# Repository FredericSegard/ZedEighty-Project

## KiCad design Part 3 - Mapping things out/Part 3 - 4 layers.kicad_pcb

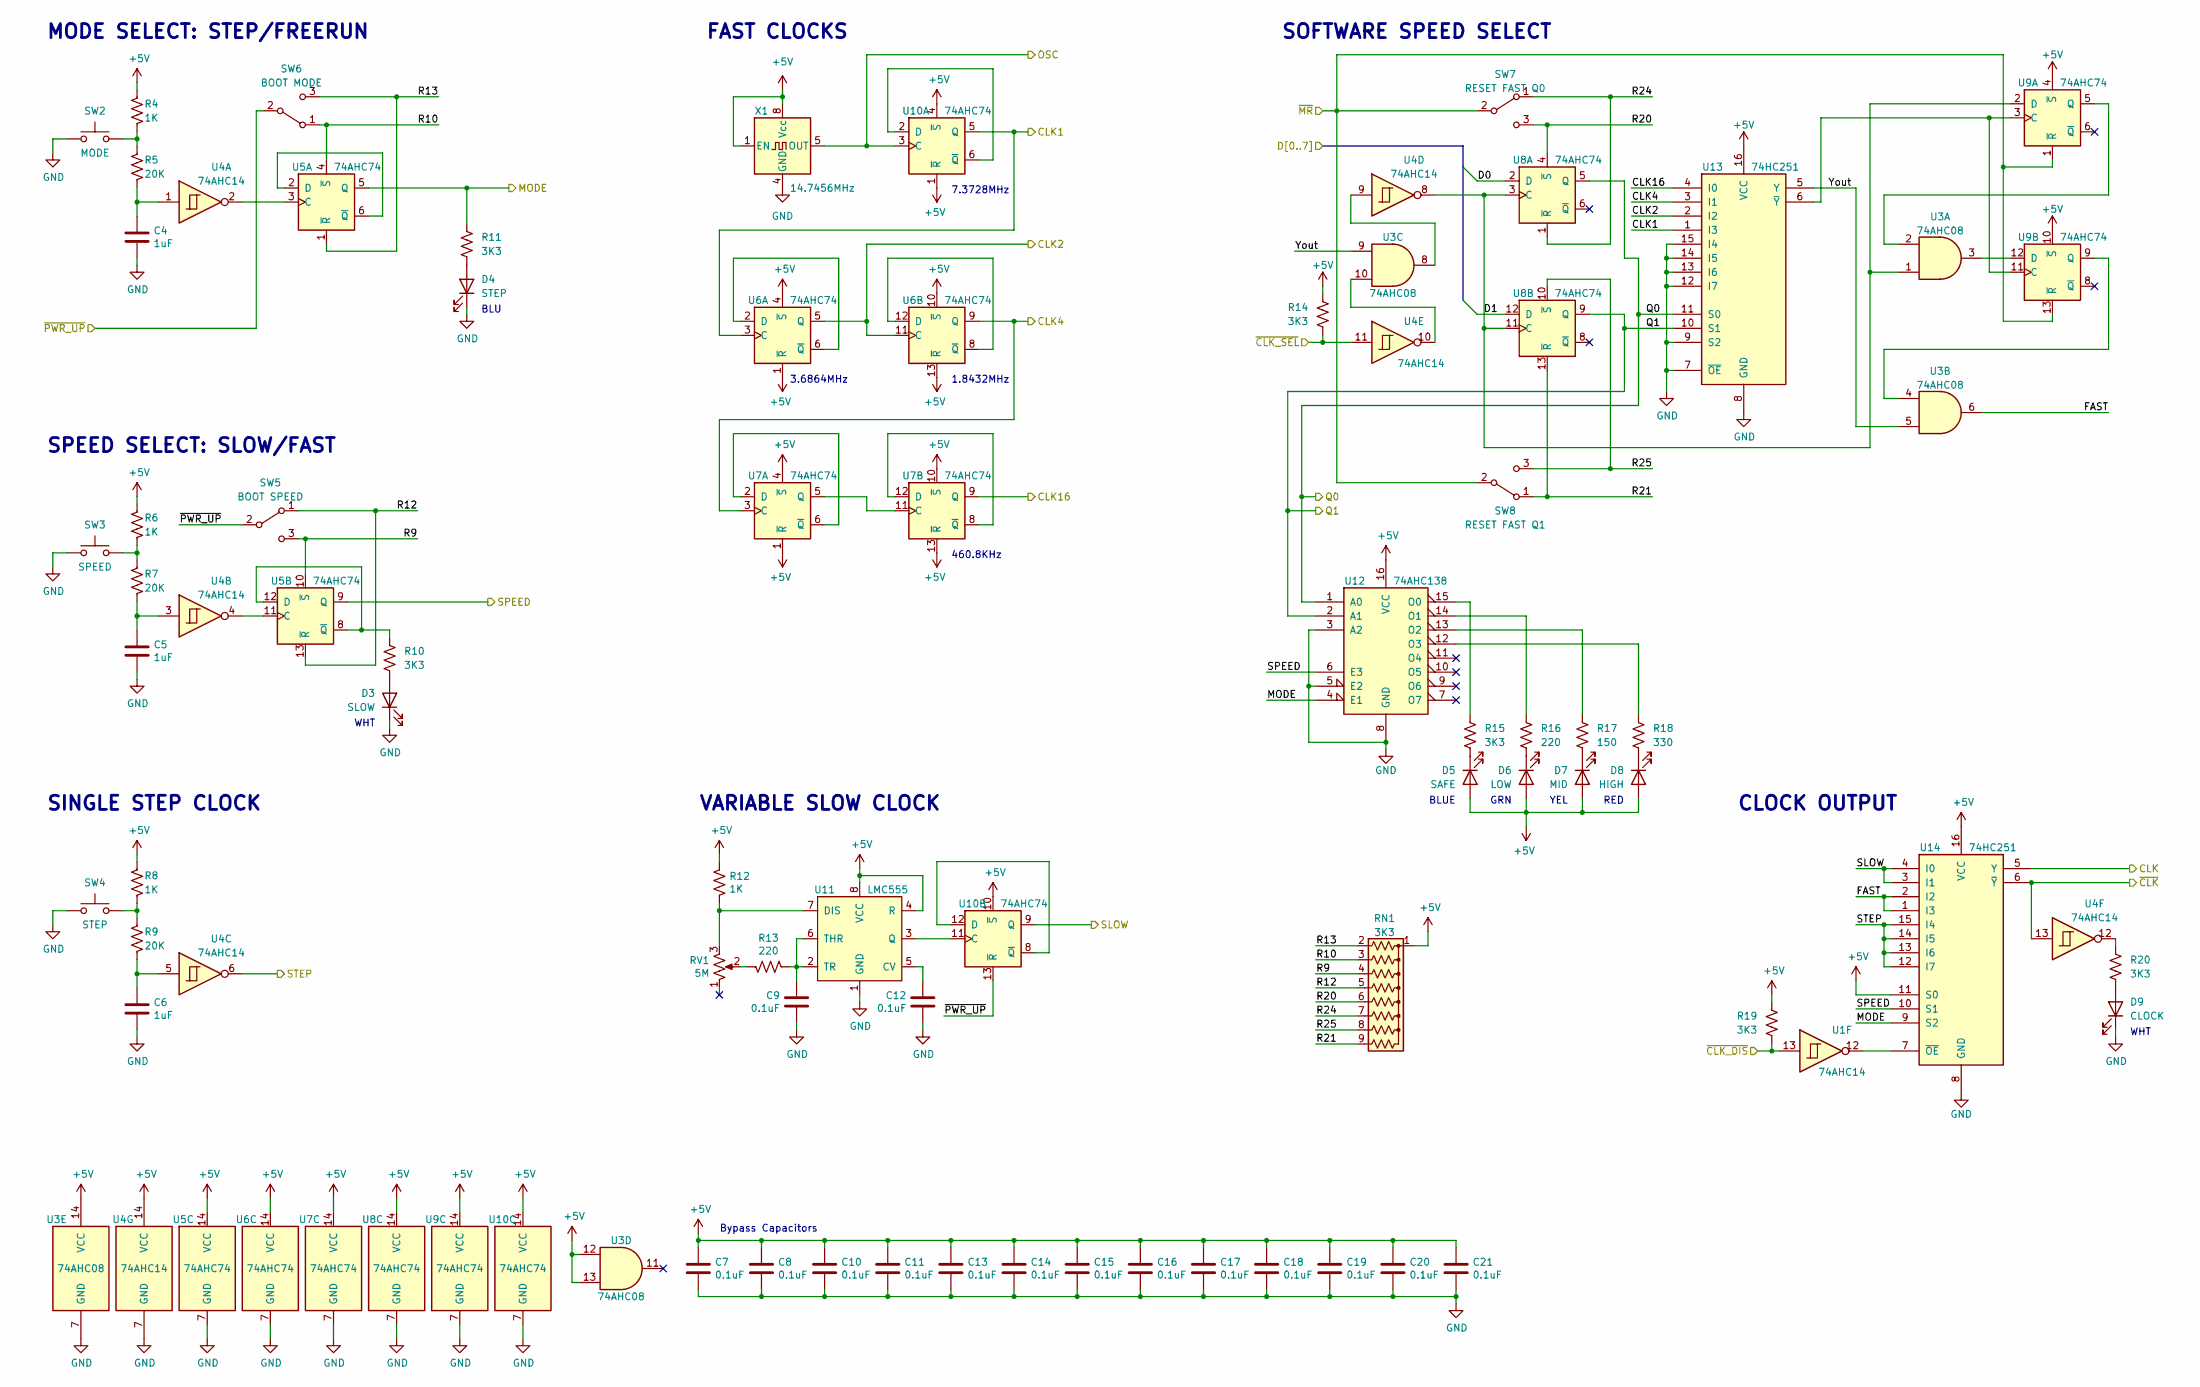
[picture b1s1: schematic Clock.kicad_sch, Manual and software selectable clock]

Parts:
C4, C5, C6: 1uF; C_Disc_D3.0mm_W1.6mm_P2.50mm
C7, C8, C9, C10, C11, C12, C13, C14, C15, C16, C17, C18, C19, C20, C21: 0.1uF; C_Disc_D3.0mm_W1.6mm_P2.50mm
D3: SLOW; LED_D3.0mm_Horizontal_O1.27mm_Z2.0mm_Clear
D4: STEP; LED_D3.0mm_Horizontal_O1.27mm_Z2.0mm_Clear
D5: SAFE; LED_D3.0mm_Horizontal_O1.27mm_Z2.0mm_Clear
D6: LOW; LED_D3.0mm_Horizontal_O1.27mm_Z2.0mm_Clear
D7: MID; LED_D3.0mm_Horizontal_O1.27mm_Z2.0mm_Clear
D8: HIGH; LED_D3.0mm_Horizontal_O1.27mm_Z2.0mm_Clear
D9: CLOCK; LED_D3.0mm_Horizontal_O1.27mm_Z2.0mm_Clear
R4, R6, R8, R12: 1K; R_Axial_DIN0207_L6.3mm_D2.5mm_P10.16mm_Horizontal
R5, R7, R9: 20K; R_Axial_DIN0207_L6.3mm_D2.5mm_P10.16mm_Horizontal
R10, R11, R14, R15, R19, R20: 3K3; R_Axial_DIN0207_L6.3mm_D2.5mm_P10.16mm_Horizontal
R13, R16: 220; R_Axial_DIN0207_L6.3mm_D2.5mm_P10.16mm_Horizontal
R17: 150; R_Axial_DIN0207_L6.3mm_D2.5mm_P10.16mm_Horizontal
R18: 330; R_Axial_DIN0207_L6.3mm_D2.5mm_P10.16mm_Horizontal
RN1: 3K3; R_Array_SIP9
RV1: 5M; Potentiometer_Bourns_3006P_Horizontal
SW2: MODE; SW_Tactile_SPST_Angled_PTS645Vx58-2LFS
SW3: SPEED; SW_Tactile_SPST_Angled_PTS645Vx58-2LFS
SW4: STEP; SW_Tactile_SPST_Angled_PTS645Vx58-2LFS
SW5: BOOT SPEED; Microswitch_4.7mm_spacing
SW6: BOOT MODE; Microswitch_4.7mm_spacing
SW7: RESET FAST Q0; Microswitch_4.7mm_spacing
SW8: RESET FAST Q1; Microswitch_4.7mm_spacing
U1, U4: 74AHC14; DIP-14_W7.62mm_Socket
U3: 74AHC08; DIP-14_W7.62mm_Socket
U5, U6, U7, U8, U9, U10: 74AHC74; DIP-14_W7.62mm_Socket
U11: LMC555; DIP-8_W7.62mm_Socket
U12: 74AHC138; DIP-16_W7.62mm_Socket
U13, U14: 74HC251; DIP-16_W7.62mm_Socket
X1: 14.7456MHz; DIP-8-4_W7.62mm_Oscillator_Socket

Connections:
/CLK: U14.5 (Y); also elsewhere on the board
/CLK1: U6.3 (C), U10.5 (Q), U13.1 (I3); also elsewhere on the board
/CLK2: U6.5 (Q), U6.11 (C), U13.2 (I2); also elsewhere on the board
/CLK4: U6.9 (Q), U7.3 (C), U13.3 (I1); also elsewhere on the board
/CLK16: U7.9 (Q), U13.4 (I0); also elsewhere on the board
/Clock/FAST: U3.6, U14.1 (I3), U14.2 (I2)
/Clock/R9: RN1.4 (R3), SW5.3 (C), U5.10 (~S)
/Clock/R10: RN1.3 (R2), SW6.1 (A), U5.4 (~S)
/Clock/R12: RN1.5 (R4), SW5.1 (A), U5.13 (~R)
/Clock/R13: RN1.2 (R1), SW6.3 (C), U5.1 (~R)
/Clock/R20: RN1.6 (R5), SW7.3 (C), U8.4 (~S)
/Clock/R21: RN1.9 (R8), SW8.1 (A), U8.13 (~R)
/Clock/R24: RN1.7 (R6), SW7.1 (A), U8.1 (~R)
/Clock/R25: RN1.8 (R7), SW8.3 (C), U8.10 (~S)
/Clock/Yout: U3.5, U3.9, U13.5 (Y)
/D0: U8.2 (D); also elsewhere on the board
/D1: U8.12 (D); also elsewhere on the board
/MODE: R11.1, U5.5 (Q), U12.4 (E1), U14.9 (S2); also elsewhere on the board
/OSC: U10.3 (C), X1.5 (OUT); also elsewhere on the board
/Q0: U8.5 (Q), U12.1 (A0), U13.11 (S0); also elsewhere on the board
/Q1: U8.9 (Q), U12.2 (A1), U13.10 (S1); also elsewhere on the board
/SLOW: U10.9 (Q), U14.3 (I1), U14.4 (I0); also elsewhere on the board
/SPEED: U5.9 (Q), U12.6 (E3), U14.10 (S1); also elsewhere on the board
/STEP: U4.6, U14.12 (I7), U14.13 (I6), U14.14 (I5), U14.15 (I4); also elsewhere on the board
/~CLK_SEL: R14.1, U4.11; also elsewhere on the board
/~CLK: U4.13, U14.6 (~Y); also elsewhere on the board
/~PWR_UP: SW5.2 (B), SW6.2 (B), U10.13 (~R); also elsewhere on the board
unnamed: C5.1, R7.1, U4.3
unnamed: C9.1, R13.2, U11.2 (TR), U11.6 (THR)
unnamed: C12.1, U11.5 (CV)
unnamed: D3.2 (A), R10.2
unnamed: D4.2 (A), R11.2
unnamed: D5.1 (K), R15.2
unnamed: D6.1 (K), R16.2
unnamed: D7.1 (K), R17.2
unnamed: D8.1 (K), R18.2
unnamed: D9.2 (A), R20.2
unnamed: R8.2, R9.2, SW4.1
unnamed: R10.1, U5.8 (~Q), U5.12 (D)
unnamed: R12.2, RV1.3, U11.7 (DIS)
unnamed: R13.1, RV1.2
unnamed: R15.1, U12.15 (O0)
unnamed: R16.1, U12.14 (O1)
unnamed: R17.1, U12.13 (O2)
unnamed: R18.1, U12.12 (O3)
unnamed: R20.1, U4.12
unnamed: U1.12, U14.7 (~OE)
unnamed: U3.1, U4.8, U8.3 (C), U8.11 (C), U9.2 (D)
unnamed: U3.2, U9.5 (Q)
unnamed: U3.3, U9.12 (D)
unnamed: U3.4, U9.9 (Q)
unnamed: U3.8, U4.9
unnamed: U3.10, U4.10
unnamed: U4.2, U5.3 (C)
unnamed: U4.4, U5.11 (C)
unnamed: U5.2 (D), U5.6 (~Q)
unnamed: U6.2 (D), U6.6 (~Q)
unnamed: U6.8 (~Q), U6.12 (D)
unnamed: U7.2 (D), U7.6 (~Q)
unnamed: U7.5 (Q), U7.11 (C)
unnamed: U7.8 (~Q), U7.12 (D)
unnamed: U10.2 (D), U10.6 (~Q)
unnamed: U10.11 (C), U11.3 (Q)
unnamed: U10.8 (~Q), U10.12 (D)
unnamed: U9.3 (C), U9.11 (C), U13.6 (~Y)

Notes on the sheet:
3.6864MHz
VARIABLE SLOW CLOCK
SPEED SELECT: SLOW/FAST
Bypass Capacitors
MODE SELECT: STEP/FREERUN
RED
FAST CLOCKS
SOFTWARE SPEED SELECT
CLOCK OUTPUT
GRN
WHT
1.8432MHz
BLU
7.3728MHz
YEL
BLUE
460.8KHz
SINGLE STEP CLOCK

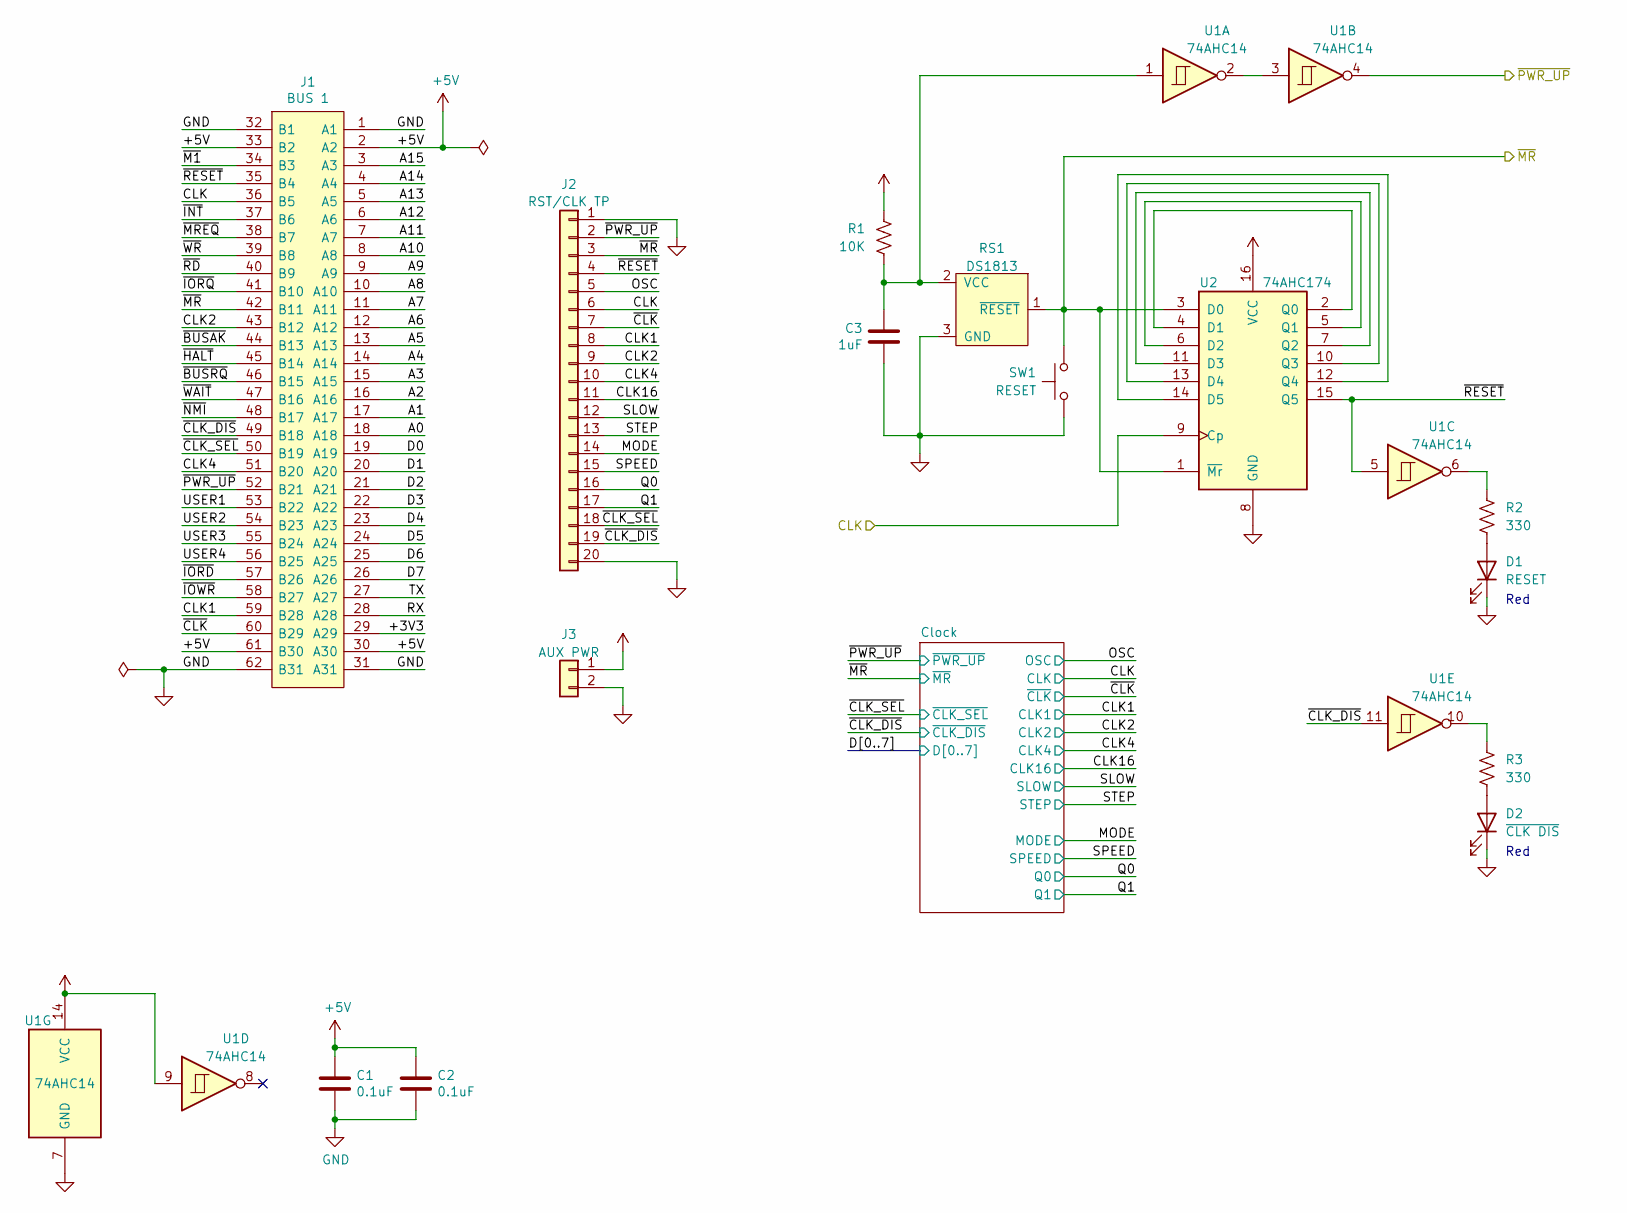
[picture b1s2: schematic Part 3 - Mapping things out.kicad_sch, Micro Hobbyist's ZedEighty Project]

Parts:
C1, C2: 0.1uF; C_Disc_D3.0mm_W2.0mm_P2.50mm
C3: 1uF; C_Disc_D3.0mm_W2.0mm_P2.50mm
D1: RESET; LED_D3.0mm_Horizontal_O1.27mm_Z2.0mm_Clear
D2: ~{CLK DIS}; LED_D3.0mm_Horizontal_O1.27mm_Z2.0mm_Clear
J1: BUS 1; BUS_XT; Mouser Part Number 571-6-5530843-5
J2: RST/CLK TP; PinSocket_1x20_P2.54mm_Horizontal
J3: AUX PWR; PinSocket_1x02_P2.54mm_Horizontal
R1: 10K; R_Axial_DIN0207_L6.3mm_D2.5mm_P10.16mm_Horizontal
R2, R3: 330; R_Axial_DIN0207_L6.3mm_D2.5mm_P10.16mm_Horizontal
RS1: DS1813; TO-92L_Inline_Wide
SW1: RESET; SW_Tactile_SPST_Angled_PTS645Vx58-2LFS
U1: 74AHC14; DIP-14_W7.62mm_Socket
U2: 74AHC174; DIP-16_W7.62mm_Socket

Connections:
/+3V3: J1.29 (A29)
/A0: J1.18 (A18)
/A1: J1.17 (A17)
/A2: J1.16 (A16)
/A3: J1.15 (A15)
/A4: J1.14 (A14)
/A5: J1.13 (A13)
/A6: J1.12 (A12)
/A7: J1.11 (A11)
/A8: J1.10 (A10)
/A9: J1.9 (A9)
/A10: J1.8 (A8)
/A11: J1.7 (A7)
/A12: J1.6 (A6)
/A13: J1.5 (A5)
/A14: J1.4 (A4)
/A15: J1.3 (A3)
/CLK: J1.36 (B5), J2.6, U2.9 (Cp); also elsewhere on the board
/CLK1: J1.59 (B28), J2.8; also elsewhere on the board
/CLK2: J1.43 (B12), J2.9; also elsewhere on the board
/CLK4: J1.51 (B20), J2.10; also elsewhere on the board
/CLK16: J2.11; also elsewhere on the board
/D0: J1.19 (A19); also elsewhere on the board
/D1: J1.20 (A20); also elsewhere on the board
/D2: J1.21 (A21)
/D3: J1.22 (A22)
/D4: J1.23 (A23)
/D5: J1.24 (A24)
/D6: J1.25 (A25)
/D7: J1.26 (A26)
/MODE: J2.14; also elsewhere on the board
/OSC: J2.5; also elsewhere on the board
/Q0: J2.16; also elsewhere on the board
/Q1: J2.17; also elsewhere on the board
/RX: J1.28 (A28)
/SLOW: J2.12; also elsewhere on the board
/SPEED: J2.15; also elsewhere on the board
/STEP: J2.13; also elsewhere on the board
/TX: J1.27 (A27)
/USER1: J1.53 (B22)
/USER2: J1.54 (B23)
/USER3: J1.55 (B24)
/USER4: J1.56 (B25)
/USER5: J1.57 (B26)
/USER6: J1.58 (B27)
/~BUSAK: J1.44 (B13)
/~BUSRQ: J1.46 (B15)
/~CLK_SEL: J1.50 (B19), J2.18; also elsewhere on the board
/~CLK: J1.60 (B29), J2.7; also elsewhere on the board
/~HALT: J1.45 (B14)
/~INT: J1.37 (B6)
/~IORQ: J1.41 (B10)
/~M1: J1.34 (B3)
/~MREQ: J1.38 (B7)
/~NMI: J1.48 (B17)
/~PWR_UP: J1.52 (B21), J2.2, U1.4; also elsewhere on the board
/~RD: J1.40 (B9)
/~RESET: J1.35 (B4), J2.4, U1.5, U2.15 (Q5)
/~WAIT: J1.47 (B16)
/~WR: J1.39 (B8)
unnamed: D1.2 (A), R2.2
unnamed: R3.1, U1.10
unnamed: U1.2, U1.3
unnamed: U2.2 (Q0), U2.4 (D1)
unnamed: U2.5 (Q1), U2.6 (D2)
unnamed: U2.10 (Q3), U2.13 (D4)
unnamed: U2.7 (Q2), U2.11 (D3)
unnamed: U2.12 (Q4), U2.14 (D5)

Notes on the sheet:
Red

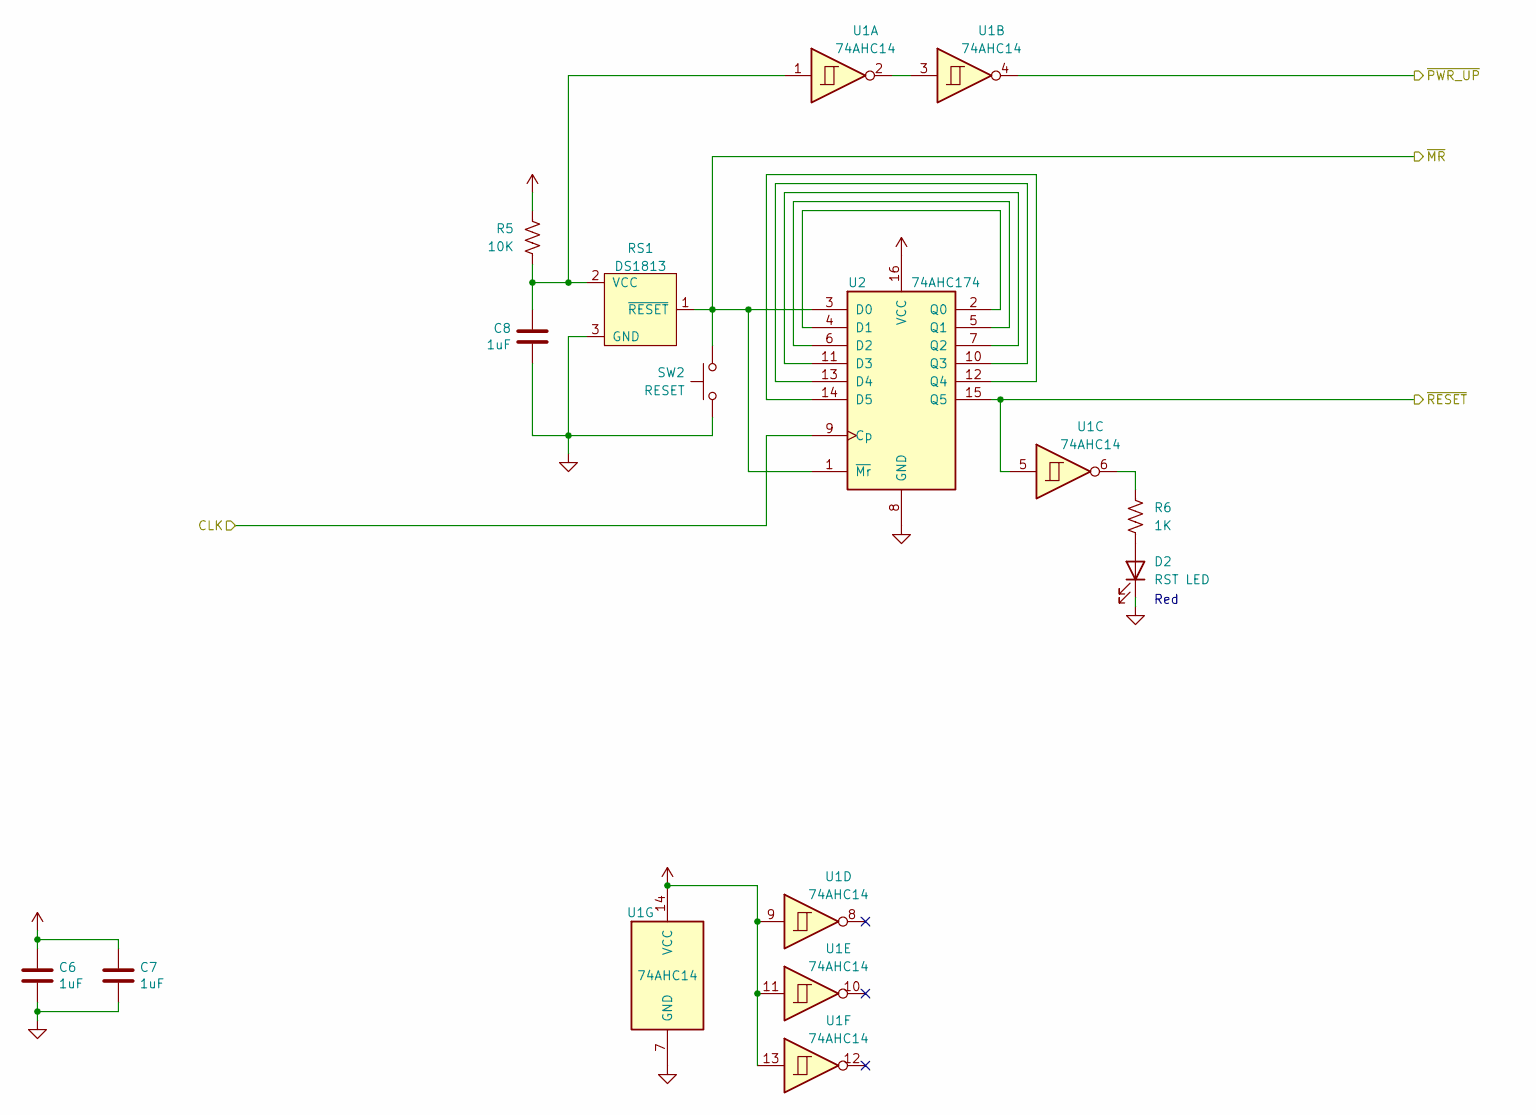
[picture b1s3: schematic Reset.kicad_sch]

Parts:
C6, C7, C8: 1uF; C_Disc_D3.0mm_W2.0mm_P2.50mm
D2: RST LED; LED_D3.0mm_Horizontal_O1.27mm_Z2.0mm_Clear
R5: 10K; R_Axial_DIN0207_L6.3mm_D2.5mm_P10.16mm_Horizontal
R6: 1K; R_Axial_DIN0207_L6.3mm_D2.5mm_P10.16mm_Horizontal
RS1: DS1813; TO-92L_Inline_Wide
SW2: RESET; SW_PUSH-12mm_Wuerth-430476085716
U1: 74AHC14; DIP-14_W7.62mm_Socket
U2: 74AHC174; DIP-16_W7.62mm_Socket

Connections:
/CLK: U2.9 (Cp); also elsewhere on the board
/~PWR_UP: U1.4; also elsewhere on the board
/~RESET: U1.5, U2.15 (Q5); also elsewhere on the board
unnamed 81: U1.10; also elsewhere on the board
unnamed: U1.2, U1.3
unnamed 92: U1.12; also elsewhere on the board
unnamed: U2.2 (Q0), U2.4 (D1)
unnamed: U2.5 (Q1), U2.6 (D2)
unnamed: U2.10 (Q3), U2.13 (D4)
unnamed: U2.7 (Q2), U2.11 (D3)
unnamed: U2.12 (Q4), U2.14 (D5)

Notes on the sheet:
Red

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
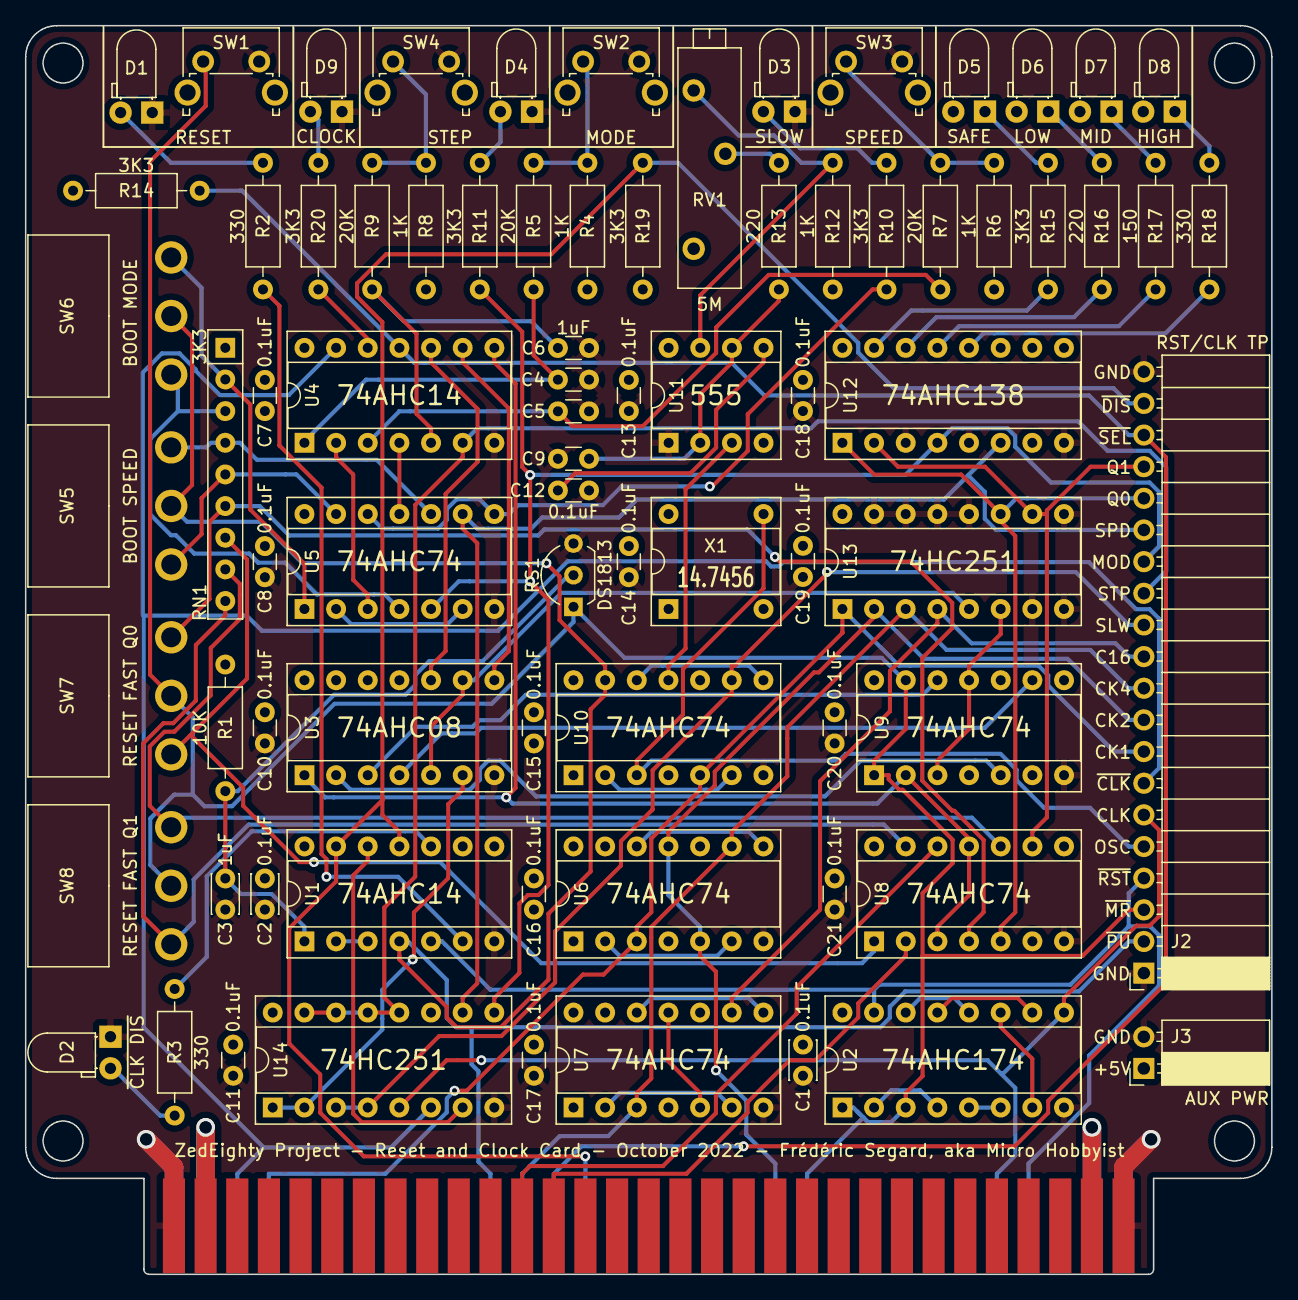
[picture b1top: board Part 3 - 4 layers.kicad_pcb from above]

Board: 4 copper layers, 100.0 x 100.2 mm, 79 parts (0 on the bottom side), 85 nets.
